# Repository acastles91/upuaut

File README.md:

# upuaut
Upuaut KiCad Project

### Explicación
El proyecto se abre desde el archivo `upuaut_2Nils.pro`. El esquemático correspondiente es `upuaut_2Nils.sch`. La nomenclatura es un desorden porque empecé a hacer el proyecto antes de saber de version control y no he reordenado todo, cuando sepa mejor por donde coger lo haré de ceros. 

En el esquemático se puede ver arriba a la izquierda el Teensy 3.2 que controla todo. Las conexiones están hechas sobre todo con `labels`. `START-STOP`, `DIRECTION-SWITCH`, `CAPTURE` y `SPEED-SELECT` son botones con interrupt. El código lo puede ver en [este repositorio](https://github.com/acastles91/Upu). El loop es en términos generales algo así:

```
volatile Request requestStream = checkInputStreamOF(Serial, prevRequest);
  if(requestStream != prevRequest){
    switchStateOF(requestStream,
                prevRequest, 
                stepperObj, 
                stepControlObj, 
                rotateControlObj, 
                sensorObj, 
                rotaryObj, 
                openCelluloidObj, 
                motorObj, 
                bounceSensor,
                leds,
                encoderObj,
                bounceEncoButton,
                triggerTimerObj,
                modeObj,
                debouncers,
                stateObj,
                bounceStartStop);
    prevRequest = requestStream;
  }

    volatile Request requestButton = checkInputButtonsOF(debouncers, prevRequest);
    if(requestButton != prevRequest){
    switchStateOF(requestButton,
                prevRequest,
                stepperObj, 
                stepControlObj, 
                rotateControlObj, 
                sensorObj, 
                rotaryObj, 
                openCelluloidObj, 
                motorObj, 
                bounceSensor,
                leds,
                encoderObj,
                bounceEncoButton,
                triggerTimerObj,
                modeObj,
                debouncers,
                stateObj,
                bounceStartStop);
     }
```
Escribí una clase que se llama `Request`. Las funciones `checkInputStreamOF()` y `checkInputButtonsOF()` tienen como `return value` un `Request`. Existe de antes un `Request` llamado `prevRequest`. Este `Request` es el valor del último `Request` del cual el programa tiene conocimiento. Si las funciones dan como `return value` algo diferente al `Request` anterior, o sea `prevRequest`, se llama la función `switchStateOF()`. Esta función cambia el estado de la máquina: la pone en movimiento, la frena, le cambia la velocidad etc. Lo fundamental es que este cambio de estado depende de la clase de `Request` que se haga, que se hace con los botones de la máquina en el caso de `checkInputButtonsOF()` o de paquetes a través del `Serial` en `checkInputStreamOF()`. Cuando hay un cambio de estado de los botones `checkInputButtonOF()` genera un `Request` distinto a `prevRequest`, y los botones tienen que tener interrupt para poder guardar este cambio de nuevo valor sin importar en qué momentodel loop suceda. 

Aparte de los botones, el Teensy tiene conectados distintos Leds que no son muy importantes para la funcionalidad. Otro punto central de la máquina es el `SENSOR`. Este sensor también tiene un `interrupt`. No recuerdo bien cómo lo solucioné en su momento, pero la idea es que el sensor de la máquina está posicionado enfrente del opturador del proyector y detecta si el opturador está o no abierto. El sensor tiene que detectar la posición del opturador independientemente de los pasos del motor. El sensor lee cambios de estado, de abierto a cerrado. Tiene que ser o 0 o 1. Todavía no estoy muy convencido del sensor que estoy usando pero eso lo podemos ver después.Cuando hay un cambio de estado el sensor le suma 1 a un contador. Cuando el contador llega a 4 el controlador manda un paquete serial al computador para que capture el frame y el contador vuelve a 0. El numero 4 tiene que ver con la forma física del opturador. Esta función de mandar el paquete tiene que ser inmediata, independiente del lugar del loop en que suceda. 

 Otro aspecto importante es el motor, que se controla con los pins `STEP`, `DIRECTION` y `ENABLE`. El modo `STEP/DIR` es relativamente sencillo, sólo se necesita que `STEP` sea capaz de `PWM` para que los pasos no interfieran con el loop. Si cambio de microcontrolador me toca encontrar librerías que manejen bien la aceleración y sean fáciles de usar. Creo que el `StepStick` debería tener un condensador en algún lugar y en el esquemátic no está. Quiero usar sobre todo controladores de Trinamics, en especial el [TMC5160] (https://www.trinamic.com/support/eval-kits/details/silentstepstick/). Para eso necesito conectarlo a por `SPI`, o sea me toca designar pins para `MISO`, `MOSI` y `CLK`. ¿Usted sabe si estos pins pueden ser cualquier pin o tienen que ser unos específicos? El `CHIP_SELECT` ya lo tengo asignado pero creo que nunca logré ponerlo en funcionamiento bien, terminé usando unos drivers que funcionan por `UART` pero que también se pueden usar por defecto en `Standalone Mode` y solo neceistan `STEP/DIR` si no se les da nada más. 

Otra funcionalidad que quedó por explorar es la que está ahi marcada como `SOUND`. El principio es que se pueda, en vez de mandar un paquete serial cada vez que hay un nuevo frame, generar un sonido y amplificarlo y mandarlo por un jack de 3.5 para conectarlo a una entrada de audio de una grabadora externa. El resultado sería un beep cada vez que haya un frame nuevo. `SHUTTER` es semejante pero para un opturador de una camara de fotos, a través de un optocoplador. 

Además de esto hay un ventilador que seguramente no funciona bien, unos reguladores de voltaje para bajar la entrade de 24V a 5V y 12V (creo que 5V sobra, la pienso cambiar a 3.3V), un Mosfet para proteger el sistema en caso de polaridad invertida y un LED muy poderoso que se controla directamente con un driver que está en el board pero que no está conectado con el microcontrolador sino que se regula con un potenciometro.

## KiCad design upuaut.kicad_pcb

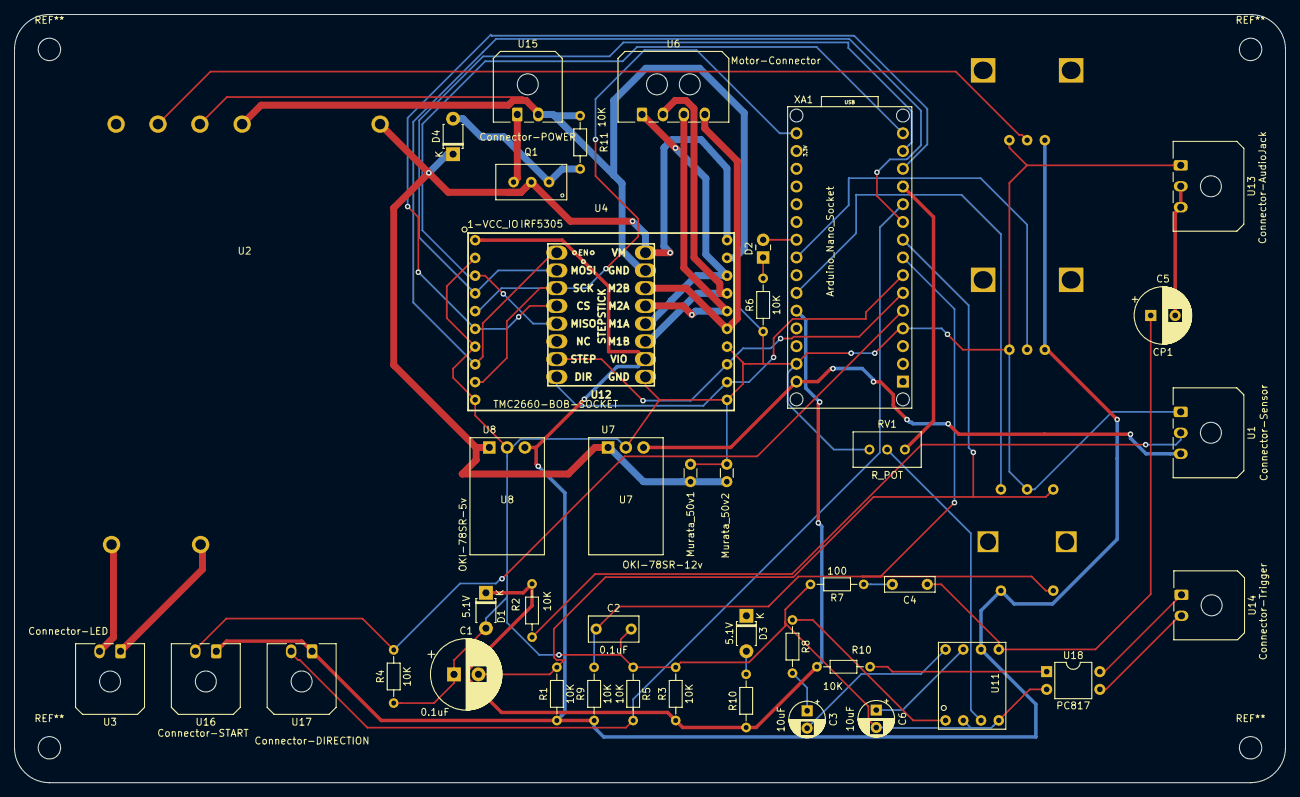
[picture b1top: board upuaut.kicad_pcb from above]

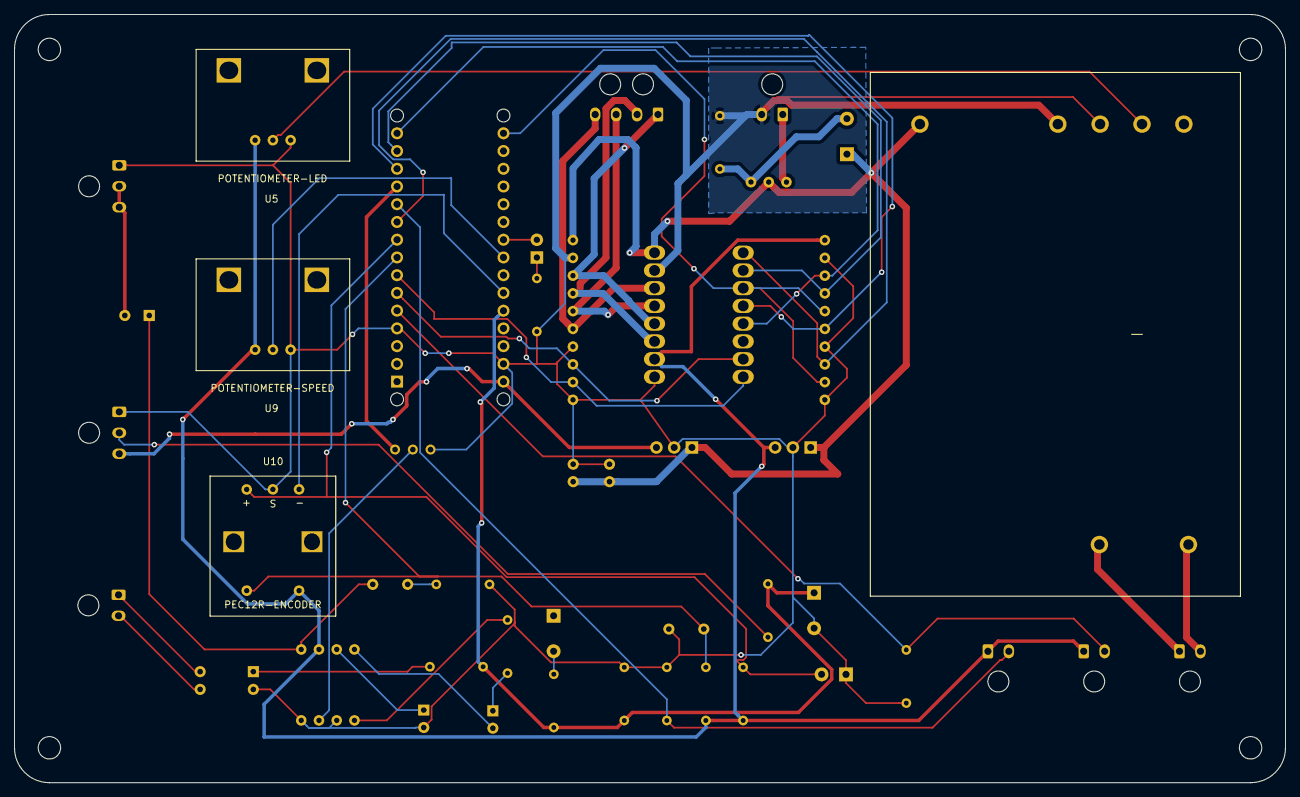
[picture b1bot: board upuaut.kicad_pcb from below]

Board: 2 copper layers, 182.0 x 110.0 mm, 45 parts (3 on the bottom side), 43 nets.

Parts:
C1: 0.1uF; CP_Radial_D10.0mm_P3.50mm
C2: 0.1uF; C_Rect_L7.0mm_W3.5mm_P5.00mm
C3, C6: 10uF; CP_Radial_D5.0mm_P2.50mm
C4: 10pF; C_Rect_L7.0mm_W2.0mm_P5.00mm
C5: CP1; CP_Radial_D8.0mm_P3.50mm
D1, D3: 5.1V; D_T-1_P5.08mm_Horizontal
D2: LED; LED_Rectangular_W3.0mm_H2.0mm
D4: 10,1V; D_T-1_P5.08mm_Horizontal
Murata_50v1, Murata_50v2: C; C_Disc_D3.0mm_W1.6mm_P2.50mm
Q1: IRF5305
R1, R2, R3, R4, R5, R6, R9, R10#2, R11: 10K; R_Axial_DIN0204_L3.6mm_D1.6mm_P7.62mm_Horizontal
R7: 100; R_Axial_DIN0204_L3.6mm_D1.6mm_P7.62mm_Horizontal
R8, R10: R; R_Axial_DIN0204_L3.6mm_D1.6mm_P7.62mm_Horizontal
RV1: R_POT; Potentiometer_Bourns_3296W_Vertical
U1: Connector-Sensor; Molex_Micro-Fit_3.0_43650-0300_1x03_P3.00mm_Horizontal
U2: LDH-45B-1050; MeanWell-LDH-45B-1050
U3: Connector-LED; Molex_Micro-Fit_3.0_43650-0200_1x02_P3.00mm_Horizontal
U4: TMC2660-BOB-SOCKET; TMC2660-BOB
U5: POTENTIOMETER-LED; PDB12-H4301-Potentiometer
U6: Motor-Connector; Molex_Micro-Fit_3.0_43650-0400_1x04_P3.00mm_Horizontal
U7: OKI-78SR-12v; Converter_DCDC_muRata_OKI-78SR_Horizontal
U8: OKI-78SR-5v; Converter_DCDC_muRata_OKI-78SR_Horizontal
U9: POTENTIOMETER-SPEED; PDB12-H4301-Potentiometer
U10: PEC12R-ENCODER; Potentiometer-BOURNS
U11: LM386
U12: STEPSTICK
U13: Connector-AudioJack; Molex_Micro-Fit_3.0_43650-0300_1x03_P3.00mm_Horizontal
U14: Connector-Trigger; Molex_Micro-Fit_3.0_43650-0200_1x02_P3.00mm_Horizontal
U15: Connector-POWER; Molex_Micro-Fit_3.0_43650-0200_1x02_P3.00mm_Horizontal
U16: Connector-START; Molex_Micro-Fit_3.0_43650-0200_1x02_P3.00mm_Horizontal
U17: Connector-DIRECTION; Molex_Micro-Fit_3.0_43650-0200_1x02_P3.00mm_Horizontal
U18: PC817; DIP-4_W7.62mm
XA1: Arduino_Nano_Socket

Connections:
5V: R1.1, R9.1, U4.1, U5.1, U8.3, U9.1, U10.4, U11.6, U12.15, U16.1, U17.1
12V: U1.3, U7.3, XA1.VIN
24V: D4.1, Murata_50v1.1, Murata_50v2.1, Q1.1, U2.5, U4.20, U7.1, U8.1, U12.9
+24V: Q1.8, U15.1
AUDIO-SIGNAL: C5.2, U13.2, U13.3
BLACK: U4.15, U6.4, U12.11
BLUE: U4.17, U6.2, U12.14
CHANNEL-A: C1.2, R1.2, U10.1, XA1.D6
CHANNEL-B: C2.1, R9.2, U10.5, XA1.D5
CHIP-SELECT: U4.6, U12.5, XA1.D10
CLOCK: U4.5, U4.9, U12.6, XA1.D13
DIRECTION: U4.12, U12.1, XA1.D4
DIRECTION-SWITCH: R5.2, U17.2, XA1.D8
ENABLE: U4.8, U12.8, XA1.D7
ENCO-BUTTON: U10.3, XA1.A6
GND: C1.1, C2.2, C6.2, D1.2, Murata_50v1.2, Murata_50v2.2, R3.2, R4.1, R5.1, R6.1, R7.2, R11.1, RV1.3, U1.1, U2.3, U2.4, U4.2, U4.7, U4.10, U4.11, U4.14, U4.19, U5.3, U7.2, U8.2, U9.3, U10.2, U11.2, U11.4, U12.10, U12.16, U13.1, U15.2, U18.2, XA1.GND1, XA1.GND2
GREEN: U4.16, U6.3, U12.12
LED: D2.2, XA1.A3
LED+: U2.7, U3.1
LED-: U2.6, U3.2
MISO-SDO: U4.3, U12.4, XA1.D12
MOSI-SDI: U4.4, U12.7, XA1.D11
unnamed: C3.1, R8.2
unnamed: C3.2, U11.8
unnamed: C4.1, C5.1, U11.5
unnamed: C4.2, R7.1
unnamed: C6.1, U11.7
unnamed: D2.1, R6.2
unnamed: D3.2, R10.2
unnamed: D4.2, Q1.4, R11.2
unnamed: R2.1, U1.2
unnamed: R8.1, U11.1
unnamed: R10#2.2, U18.1
unnamed: RV1.2, U11.3
unnamed: U14.1, U18.4
unnamed: U14.2, U18.3
POTI-LED: U2.2, U5.2
POTI-SPEED: U9.2, XA1.A4
RED: U4.18, U6.1, U12.13
SHUTTER: D1.1, R2.2, R3.1, R10.1, R10#2.1, XA1.A7
SOUND-TRIGGER: RV1.1, XA1.D9
START-STOP: R4.2, U16.2, XA1.D2
STEP: U4.13, U12.2, XA1.D3

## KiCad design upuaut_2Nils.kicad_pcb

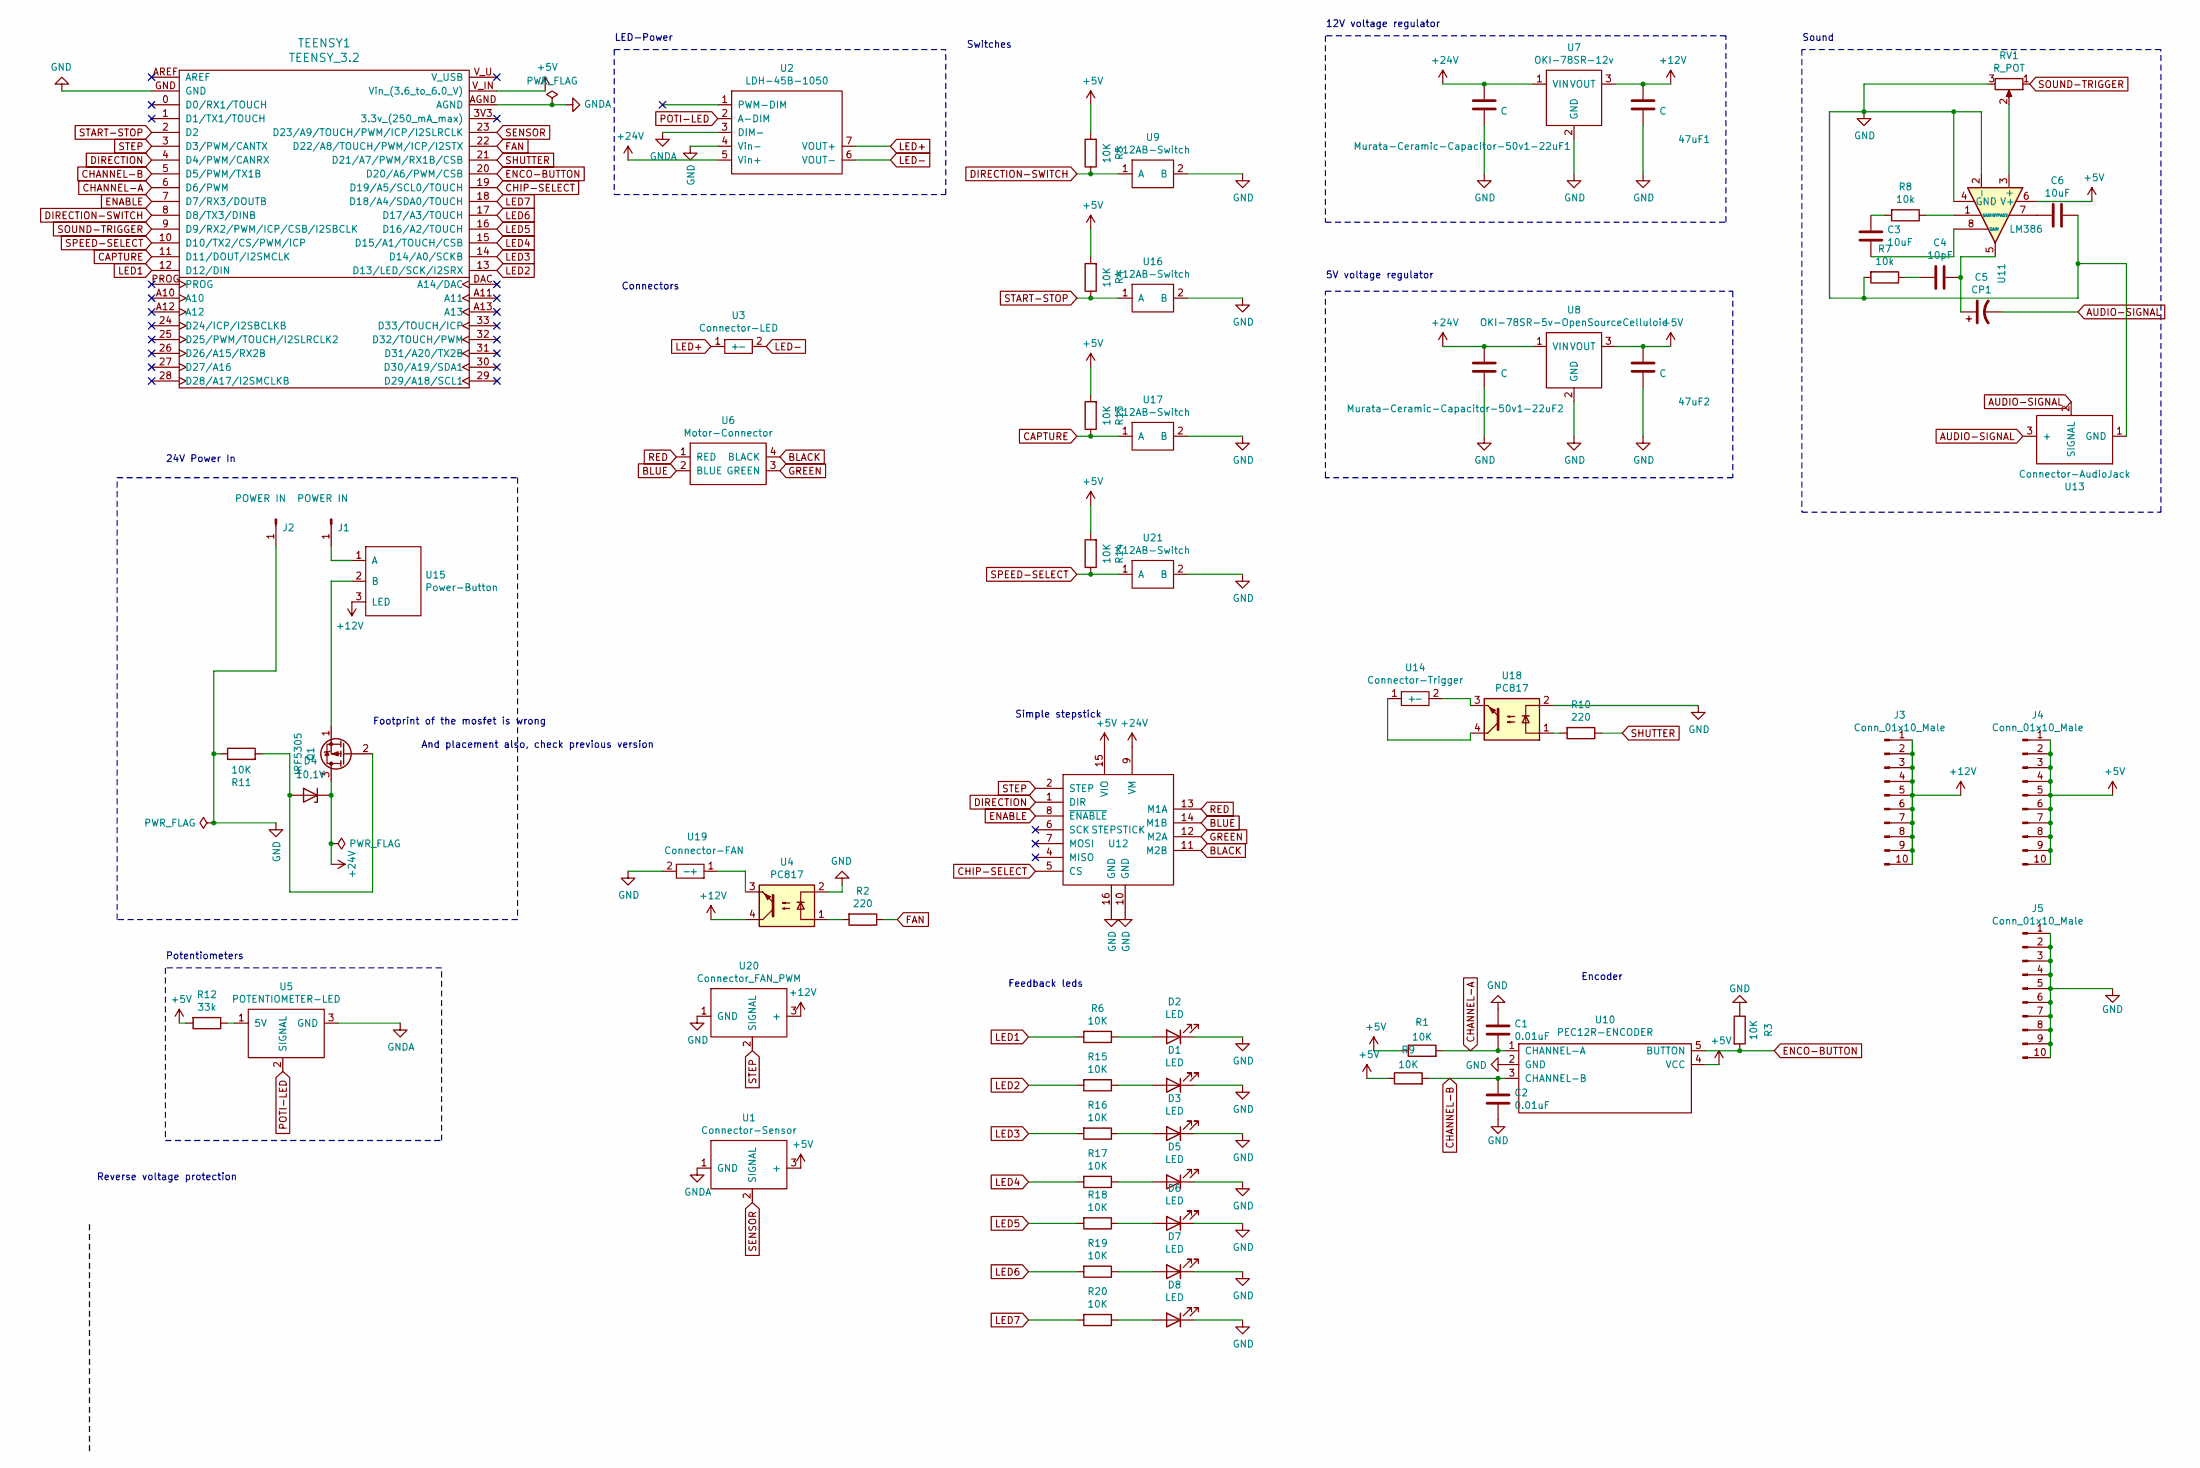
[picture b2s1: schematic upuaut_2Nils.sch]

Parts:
47uF1, 47uF2: C; C_Disc_D3.0mm_W1.6mm_P2.50mm
C1, C2: 0.01uF; C_Rect_L7.0mm_W3.5mm_P5.00mm
C3, C6: 10uF; CP_Radial_D5.0mm_P2.50mm
C4: 10pF; C_Rect_L7.0mm_W2.0mm_P5.00mm
C5: CP1; CP_Radial_D5.0mm_P2.50mm
D1, D2, D3, D5, D6, D7, D8: LED; LED_Rectangular_W3.0mm_H2.0mm
D4: 10,1V; D_T-1_P5.08mm_Horizontal
J1, J2: POWER IN; WAGO_PCB_Klemme_1Pol
J3, J4, J5: Conn_01x10_Male; PinHeader_1x10_P2.54mm_Vertical
Murata-Ceramic-Capacitor-50v1-22uF1, Murata-Ceramic-Capacitor-50v1-22uF2: C; C_Disc_D3.0mm_W1.6mm_P2.50mm
Q1: IRF5305
R1, R3, R4, R5, R6, R9, R11, R13, R14, R15, R16, R17, R18, R19, R20: 10K; R_Axial_DIN0204_L3.6mm_D1.6mm_P7.62mm_Horizontal
R2, R10: 220; R_Axial_DIN0204_L3.6mm_D1.6mm_P7.62mm_Horizontal
R7, R8: 10k; R_Axial_DIN0204_L3.6mm_D1.6mm_P7.62mm_Horizontal
R12: 33k; R_Axial_DIN0204_L3.6mm_D1.6mm_P7.62mm_Horizontal
RV1: R_POT; Potentiometer_Bourns_3296W_Vertical
TEENSY1: TEENSY_3.2
U1: Connector-Sensor; Molex_Micro-Fit_3.0_43650-0300_1x03_P3.00mm_Horizontal
U2: LDH-45B-1050; MeanWell-LDH-45B-1050
U3: Connector-LED; Molex_Micro-Fit_3.0_43650-0200_1x02_P3.00mm_Horizontal
U4, U18: PC817; DIP-4_W7.62mm
U5: POTENTIOMETER-LED; PDB12-H4301-Potentiometer
U6: Motor-Connector; Molex_Micro-Fit_3.0_43650-0400_1x04_P3.00mm_Horizontal
U7: OKI-78SR-12v; Converter_DCDC_muRata_OKI-78SR_Vertical
U8: OKI-78SR-5v-OpenSourceCelluloid; Converter_DCDC_muRata_OKI-78SR_Vertical
U9, U16, U17, U21: K12AB-Switch
U10: PEC12R-ENCODER; Potentiometer-BOURNS
U11: LM386
U12: STEPSTICK
U13: Connector-AudioJack; WAGO_PCB_Klemme_3Pol
U14: Connector-Trigger; WAGO_PCB_Klemme_2Pol
U15: Power-Button; WAGO_PCB_Klemme_3Pol
U19: Connector-FAN; WAGO_PCB_Klemme_2Pol
U20: Connector_FAN_PWM; WAGO_PCB_Klemme_3Pol

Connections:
+5V: 47uF2.1, J4.1, J4.2, J4.3, J4.4, J4.5, J4.6, J4.7, J4.8, J4.9, J4.10, R1.1, R4.2, R5.2, R9.1, R12.2, R13.2, R14.2, TEENSY1.V_IN (Vin_(3.6_to_6.0_V)), U1.3 (+), U8.3 (VOUT), U10.4 (VCC), U11.6 (V+), U12.15 (VIO)
+12V: 47uF1.1, J3.1, J3.2, J3.3, J3.4, J3.5, J3.6, J3.7, J3.8, J3.9, J3.10, U4.4, U7.3 (VOUT), U15.3 (LED), U20.3 (+)
+24V: D4.1 (K), Murata-Ceramic-Capacitor-50v1-22uF1.1, Murata-Ceramic-Capacitor-50v1-22uF2.1, Q1.3 (D), U2.5 (Vin+), U7.1 (VIN), U8.1 (VIN), U12.9 (VM)
AUDIO-SIGNAL: C5.2, U13.2 (SIGNAL), U13.3 (+)
BLACK: U6.4 (BLACK), U12.11 (M2B)
BLUE: U6.2 (BLUE), U12.14 (M1B)
CAPTURE: R13.1, TEENSY1.11 (D11/DOUT/I2SMCLK), U17.1 (A)
CHANNEL-A: C1.2, R1.2, TEENSY1.6 (D6/PWM), U10.1 (CHANNEL-A)
CHANNEL-B: C2.1, R9.2, TEENSY1.5 (D5/PWM/TX1B), U10.3 (CHANNEL-B)
CHIP-SELECT: TEENSY1.19 (D19/A5/SCL0/TOUCH), U12.5 (CS)
DIRECTION: TEENSY1.4 (D4/PWM/CANRX), U12.1 (DIR)
DIRECTION-SWITCH: R5.1, TEENSY1.8 (D8/TX3/DINB), U9.1 (A)
ENABLE: TEENSY1.7 (D7/RX3/DOUTB), U12.8 (~ENABLE)
ENCO-BUTTON: R3.2, TEENSY1.20 (D20/A6/PWM/CSB), U10.5 (BUTTON)
FAN: R2.1, TEENSY1.22 (D22/A8/TOUCH/PWM/ICP/I2STX)
GND: 47uF1.2, 47uF2.2, C1.1, C2.2, C6.2, D1.1 (K), D2.1 (K), D3.1 (K), D5.1 (K), D6.1 (K), D7.1 (K), D8.1 (K), J2.1, J5.1, J5.2, J5.3, J5.4, J5.5, J5.6, J5.7, J5.8, J5.9, J5.10, Murata-Ceramic-Capacitor-50v1-22uF1.2, Murata-Ceramic-Capacitor-50v1-22uF2.2, R3.1, R7.2, R11.1, RV1.3, TEENSY1.GND, U2.4 (Vin-), U4.2, U7.2 (GND), U8.2 (GND), U9.2 (B), U10.2 (GND), U11.2 (-), U11.4 (GND), U12.10 (GND), U12.16 (GND), U13.1 (GND), U16.2 (B), U17.2 (B), U18.2, U19.2 (-), U20.1 (GND), U21.2 (B)
GNDA: TEENSY1.AGND, U1.1 (GND), U2.3 (DIM-), U5.3 (GND)
GREEN: U6.3 (GREEN), U12.12 (M2A)
LED1: R6.2, TEENSY1.12 (D12/DIN)
LED2: R15.2, TEENSY1.13 (D13/LED/SCK/I2SRX)
LED3: R16.2, TEENSY1.14 (D14/A0/SCKB)
LED4: R17.2, TEENSY1.15 (D15/A1/TOUCH/CSB)
LED5: R18.2, TEENSY1.16 (D16/A2/TOUCH)
LED6: R19.2, TEENSY1.17 (D17/A3/TOUCH)
LED7: R20.2, TEENSY1.18 (D18/A4/SDA0/TOUCH)
LED+: U2.7 (VOUT+), U3.1 (+)
LED-: U2.6 (VOUT-), U3.2 (-)
unnamed: C3.1, R8.2
unnamed: C3.2, U11.8 (GAIN)
unnamed: C4.1, C5.1, U11.5
unnamed: C4.2, R7.1
unnamed: C6.1, U11.7 (BYPASS)
unnamed: D1.2 (A), R15.1
unnamed: D2.2 (A), R6.1
unnamed: D3.2 (A), R16.1
unnamed: D4.2 (A), Q1.2 (G), R11.2
unnamed: D5.2 (A), R17.1
unnamed: D6.2 (A), R18.1
unnamed: D7.2 (A), R19.1
unnamed: D8.2 (A), R20.1
unnamed: J1.1, U15.1 (A)
unnamed: Q1.1 (S), U15.2 (B)
unnamed: R2.2, U4.1
unnamed: R8.1, U11.1 (GAIN)
unnamed: R10.2, U18.1
unnamed: R12.1, U5.1 (5V)
unnamed: RV1.2, U11.3 (+)
unnamed: U14.1 (+), U18.4
unnamed: U14.2 (-), U18.3
unnamed: U4.3, U19.1 (+)
POTI-LED: U2.2 (A-DIM), U5.2 (SIGNAL)
RED: U6.1 (RED), U12.13 (M1A)
SENSOR: TEENSY1.23 (D23/A9/TOUCH/PWM/ICP/I2SLRCLK), U1.2 (SIGNAL)
SHUTTER: R10.1, TEENSY1.21 (D21/A7/PWM/RX1B/CSB)
SOUND-TRIGGER: RV1.1, TEENSY1.9 (D9/RX2/PWM/ICP/CSB/I2SBCLK)
SPEED-SELECT: R14.1, TEENSY1.10 (D10/TX2/CS/PWM/ICP), U21.1 (A)
START-STOP: R4.1, TEENSY1.2 (D2), U16.1 (A)
STEP: TEENSY1.3 (D3/PWM/CANTX), U12.2 (STEP), U20.2 (SIGNAL)

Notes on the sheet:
Reverse voltage protection
Sound
Encoder
12V voltage regulator
5V voltage regulator
Feedback leds
Switches
Simple stepstick
Potentiometers
LED-Power
Connectors
24V Power In
Footprint of the mosfet is wrong
And placement also, check previous version

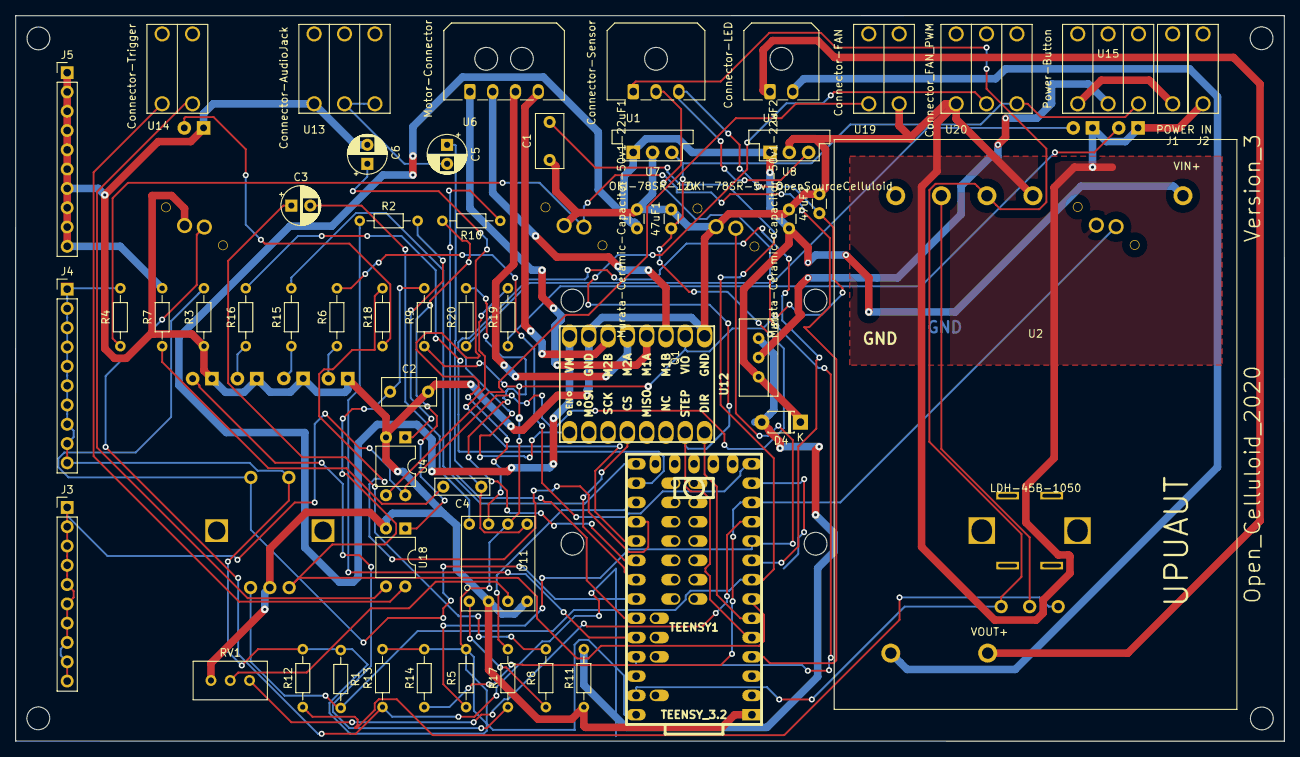
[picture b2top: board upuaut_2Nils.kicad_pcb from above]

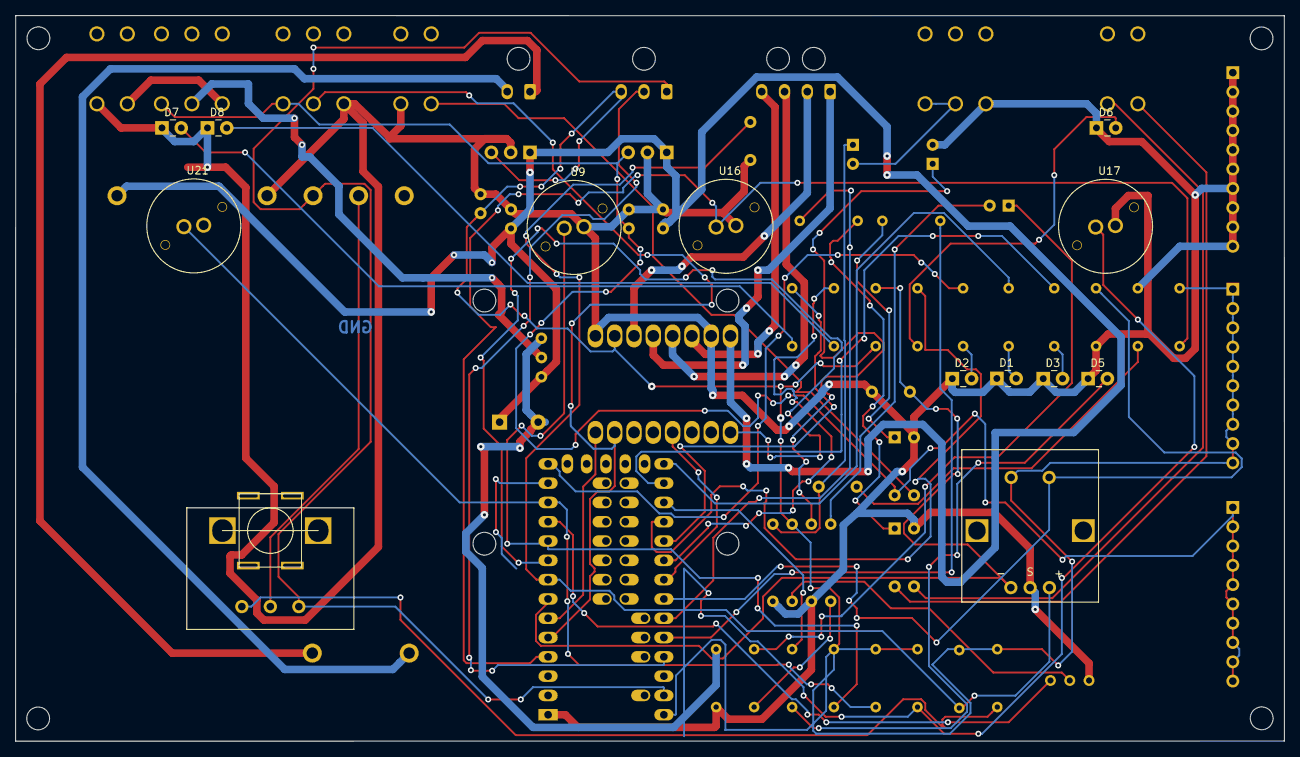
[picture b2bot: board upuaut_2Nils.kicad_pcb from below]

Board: 2 copper layers, 167.0 x 95.5 mm, 67 parts (13 on the bottom side), 58 nets.

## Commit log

2019-10-01 upuaut first!
2019-10-01 First Session
2020-12-20 December 2020
2020-12-20 let's try
2020-12-20 Readme attempt
2020-12-20 Readme updated
